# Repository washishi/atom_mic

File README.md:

# Atom MIC  
## M5Stack Atomシリーズ（ECHO,Uを除く）専用のマイク基板です  
・取り付けることによりPDMマイクの利用が可能です  
・PDMマイクは[Knowles](https://www.ja.knowles.com/)社の[SPH0641LM4H-1](https://www.knowles.com/docs/default-source/default-document-library/sph0641lm4h-1-datasheet-rev-f.pdf)を利用しています  
・Groveコネクタを1つ増設することもできます (J5)  
・各信号ピンはさらに別へも接続できるように端子が設けられています(J3,J4)  

<br>

<br>
### なお本基板は完成品(Groveコネクタは未実装で添付)をBOOTH[ わしししょっぷ ](https://washishi.booth.pm/)で頒布もしております [Atom MIC](https://washishi.booth.pm/items/6182811)
<br>

# ソフトウエアでの利用について
接続先GPIOが異なる以外は M5Stackの[PDMマイクユニット](https://docs.m5stack.com/ja/unit/pdm)と同等に利用できます

# 使用するGPIO
マイク等の接続先は下記となります　(※マイクの接続先はAtomECHOとは異なります)  

|Atom種別|MIC Clock|MIC Data|Grove PIN1|Grove PIN2|Grove PIN3|Grove PIN4|
|:--|:-:|:-:|:-:|:-:|:-:|:-:|  
|AtomS3/S3Lite/S3R/S3RCAM/S3RExt|G5|G6|G7|G8|+5V|GND|
|Atom/Atom Lite/Atom Matrix|G22|G19|G23|G33|+5V|GND|
||

また各ピンの隣のランド(J3,J4)はそれぞれ同じピンに接続されていますので  
さらに別へ接続したい場合や接続先ピンの変更等に利用できます  
# 接続先ピン変更、マイクデータのタイミング変更について
JP1のパターンカットおよび接続変更によりPDMマイクのデータタイミングの変更ができます  
(元々PDMマイクは同じバス上にデータタイミングの異なる2つのマイクが接続できる仕様となっています)  
また各接続先はJP2～JP5のパターンカットにより切り離せるようになっており  
切り離して下図の赤色側のランドをUEW線等で別のピンに繋ぐことにより接続先を変更することができます  

|JP|用途|説明|
|:--|-|:--|  
|JP1|マイク Select|デフォルトは中央の端子がGND(▽側)に繋がっていますがパターンカットして反対側(3V3)に繋ぐことによりデータタイミングが変わります|  
|JP2|マイク Clock|PDMマイクのClockピンへの接続|  
|JP3|マイク Data |PDMマイクのDataピンへの接続|   
|JP4|Grove PIN1 |Groveコネクタ(J5)のPIN1(白)への接続|    
|JP5|Grove PIN2 |Groveコネクタ(J5)のPIN2(黄)への接続|    

# 回路図
<br>
本リポジトリ schematics の下に KiCad(Ver7)で作成したデータ一式があります

# BOM(部品リスト)
|名称|仕様|メーカー|個数|備考|備考購入先|  
|:--|:-:|:-:|:-:|:-:|:-:|  
|基板|Atom MIC基板|-|1||[JLCPCB](https://jlcpcb.com/JPV)へ発注|
|PDMマイク|SPH0641LM4H-1|Knowles|1||[マルツ](https://www.marutsu.co.jp/pc/i/46506093/)(DigiKey在庫品)|  
|チップ積層セラミックコンデンサ|0.1uF 1608サイズ|-|1||[秋月電子](https://akizukidenshi.com/catalog/g/g113071/)100個セット|
|ピンヘッダ|2.54mm 1x40 ロープロファイル(9.54mm)|-|1||[秋月電子](https://akizukidenshi.com/catalog/g/g100171/)|
|Groveコネクタ|HY2.0-4P L形|-|1|Groveポートをつける場合|[秋月電子](https://akizukidenshi.com/catalog/g/g112634/)10個セット|

## 部品について
- 基板  
  本リポジトリの schematics\production に JLCPCB 向けのガーバデータがあるのでそれを利用して発注してください  
  - atom-mic.zip : 1枚のデータ (JLCPCBでは$2(送料別)で5枚の基板が作れます)  
  - atom-mic_x30.zip : 5x6の面付けデータ (JLCPCBでは$7.9(送料別)で150枚の基板が作れます)
- PDMマイク  
[SPH0641LM4H-1](https://www.knowles.com/docs/default-source/default-document-library/sph0641lm4h-1-datasheet-rev-f.pdf) を利用しています 
Degikey等で扱っていますが直接だと少量の購入では送料の方がかなり高くなると思います  
[マルツの通販](https://www.marutsu.co.jp/)でDegikey取り扱い品も注文出来てかつマルツ取扱製品も含めトータル3000円以上だと送料が無料になるので他に欲しい物と合わせて購入するとお得です。また店舗引き取りも利用可能な様です(この場合は少額でも送料無料)  
SPH0641LM4H-1の代わりに上位版の超音波まで対応できる [SPH0641LU4H-1](https://www.knowles.com/docs/default-source/model-downloads/sph0641lu4h-1-revb.pdf?Status=Master&sfvrsn=bdc077b1_4) でも利用可能です  
(こちらは[秋月電子で扱っている](https://akizukidenshi.com/catalog/g/g114730/)のですが現在は通販のみ・在庫限り・1回での購入制限1個で終売になる様です)
- チップ積層セラミックコンデンサ  
1608サイズの 0.1uF であればなんでもかまいません 耐圧は電源が3.3Vなので気にしなくてもいいと思います
- ピンヘッダ  
折って基板1枚当たり 4Pin x 1、5Pin x1 を使います  
Atomに刺した際にピン部分が余らない様にロープロファイルの物を利用しており秋月電子等で購入可能ですが  
普通のピンヘッダをラジオペンチ等で挟んで少しAtomの刺さる側を短くしてもいいと思います  
(基板側はピンを切るので長くなっても問題ないです)
- Groveコネクタ (オプション)  
  Groveポートを増やしたい場合はL形の物を準備してください

# 制作について
- マイク  
  背面にしか端子のないチップ部品の為リフローする必要がある為ヒートテーブルやクリームはんだが必要です  
  また非常に熱に弱いためクリームはんだは低温(138℃)で溶けるものを利用し短時間で済ませて下さい
- チップ積層セラミックコンデンサ  
  極性はありません 手はんだも可能ですがマイクと一緒にリフローして取り付けるといいと思います
- ピンヘッダ  
  Atomに刺すため折って 1つ当たり 4Pin x 1、5Pin x1 を準備してください  
  ロープロファイルの物が準備できない場合はそのままだと奥まで刺さらず隙間ができます(写真1枚目)  
  その場合はラジオペンチ等で挟んで刺した際にピン部分が余らない様にピンを移動してください(写真2枚目)  
  ピンが奥まで刺さった状態(写真3枚目)  

  <br>
  その後2つともAtomに刺して基板を載せて余ったピンをニッパーで切断します(写真1枚目) ※切ったピンが飛ぶので注意  
  全てのピンの余分部分を切った状態(写真2枚目)  
  この状態ではんだ付けを行います (スルーホールにしっかりはんだが流れ込むように)     
   ※あまり長時間ハンダゴテを当てるとAtomが壊れることがあるかもしれないので注意  
  
  <br>
- Groveコネクタ (オプション：取り付けると出っ張る為お好みで)  
  使う場合は写真の向きではんだ付けします  
  ピンの余った部分を切る場合ははんだ付け前に切って下さい (干渉しないのでそのままでもかまいません)  
  
  <br>

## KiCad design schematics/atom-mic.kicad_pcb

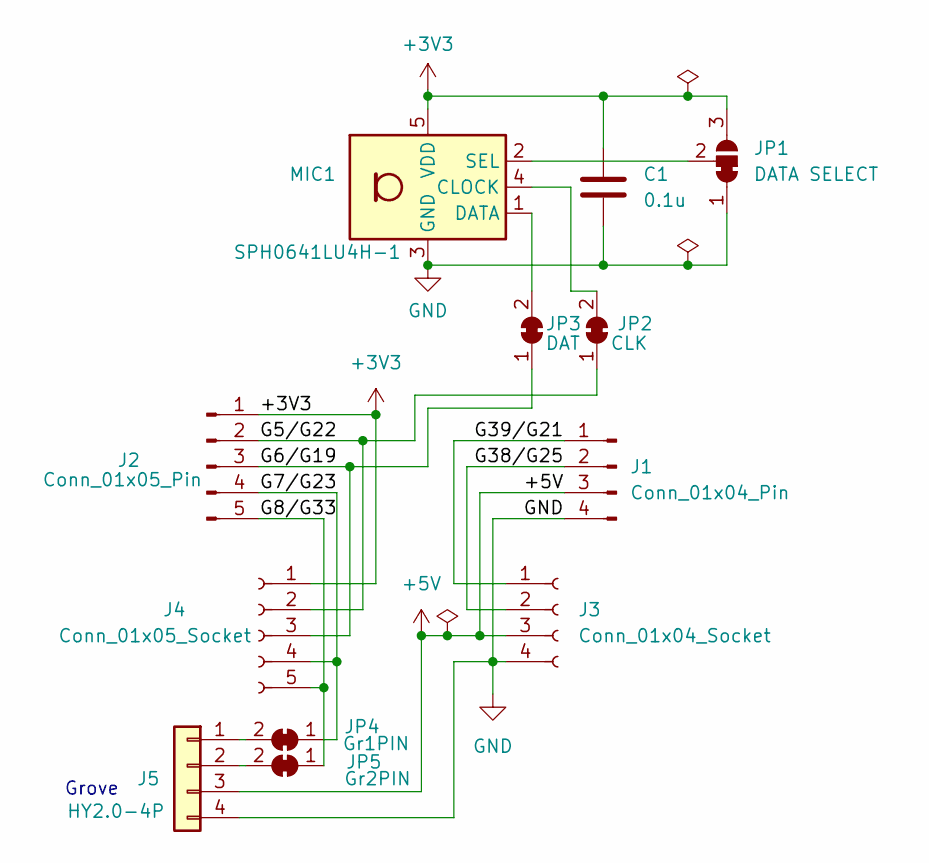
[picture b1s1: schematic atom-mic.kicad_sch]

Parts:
C1: 0.1u; C_0603_1608Metric_Pad1.08x0.95mm_HandSolder
J1: Conn_01x04_Pin; PinHeader_1x04_P2.54mm_Vertical
J2: Conn_01x05_Pin; PinHeader_1x05_P2.54mm_Vertical
J3: Conn_01x04_Socket; PinSocket_1x04_P2.54mm_Vertical
J4: Conn_01x05_Socket; PinSocket_1x05_P2.54mm_Vertical
J5: HY2.0-4P; CON_GROVE_H
JP1: DATA SELECT; SolderJumper-3_P1.3mm_Bridged12_RoundedPad1.0x1.5mm
JP2: CLK; SolderJumper-2_P1.3mm_Bridged_RoundedPad1.0x1.5mm
JP3: DAT; SolderJumper-2_P1.3mm_Bridged_RoundedPad1.0x1.5mm
JP4: Gr1PIN; SolderJumper-2_P1.3mm_Bridged_RoundedPad1.0x1.5mm
JP5: Gr2PIN; SolderJumper-2_P1.3mm_Bridged_RoundedPad1.0x1.5mm
MIC1: SPH0641LU4H-1; Knowles_LGA-5_3.5x2.65mm

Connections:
+3V3: C1.1, J2.1, J4.1, JP1.3 (B), MIC1.5 (VDD)
+5V: J1.3, J3.3, J5.3
/G5/G22: J2.2, J4.2, JP2.1 (A)
/G6/G19: J2.3, J4.3, JP3.1 (A)
/G7/G23: J2.4, J4.4, JP4.1 (A)
/G8/G33: J2.5, J4.5, JP5.1 (A)
/G38/G25: J1.2, J3.2
/G39/G21: J1.1, J3.1
GND: C1.2, J1.4, J3.4, J5.4, JP1.1 (A), MIC1.3 (GND)
unnamed: J5.1, JP4.2 (B)
unnamed: J5.2, JP5.2 (B)
unnamed: JP1.2 (C), MIC1.2 (SEL)
unnamed: JP2.2 (B), MIC1.4 (CLOCK)
unnamed: JP3.2 (B), MIC1.1 (DATA)

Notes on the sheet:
Grove

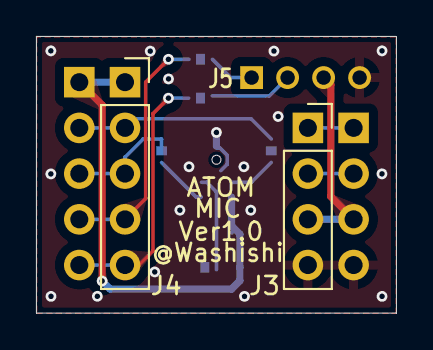
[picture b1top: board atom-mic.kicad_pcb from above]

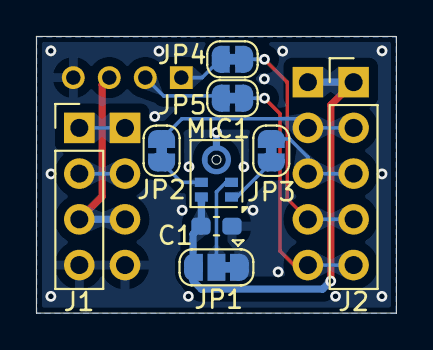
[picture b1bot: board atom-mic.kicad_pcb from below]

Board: 2 copper layers, 20.0 x 15.4 mm, 12 parts (9 on the bottom side), 14 nets.

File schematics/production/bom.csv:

Designator,Footprint,Quantity,Value,LCSC Part #
C1,0603,1,0.1u,
J1,PinHeader_1x04_P2.54mm_Vertical,1,Conn_01x04_Pin,
J2,PinHeader_1x05_P2.54mm_Vertical,1,Conn_01x05_Pin,
J3,PinSocket_1x04_P2.54mm_Vertical,1,Conn_01x04_Socket,
J4,PinSocket_1x05_P2.54mm_Vertical,1,Conn_01x05_Socket,
J5,CON_GROVE_H,1,HY2.0-4P,
JP1,SolderJumper-3_P1.3mm_Bridged12_RoundedPad1.0x1.5mm,1,DATA SELECT,
JP2,SolderJumper-2_P1.3mm_Bridged_RoundedPad1.0x1.5mm,1,CLK,
JP3,SolderJumper-2_P1.3mm_Bridged_RoundedPad1.0x1.5mm,1,DAT,
JP4,SolderJumper-2_P1.3mm_Bridged_RoundedPad1.0x1.5mm,1,Gr1PIN,
JP5,SolderJumper-2_P1.3mm_Bridged_RoundedPad1.0x1.5mm,1,Gr2PIN,
MIC1,Knowles_LGA-5_3.5x2.65mm,1,SPH0641LU4H-1,
